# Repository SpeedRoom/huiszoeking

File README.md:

# huiszoeking
Meer info over het project is te vinden op https://speedroom.github.io/Huiszoeking.html

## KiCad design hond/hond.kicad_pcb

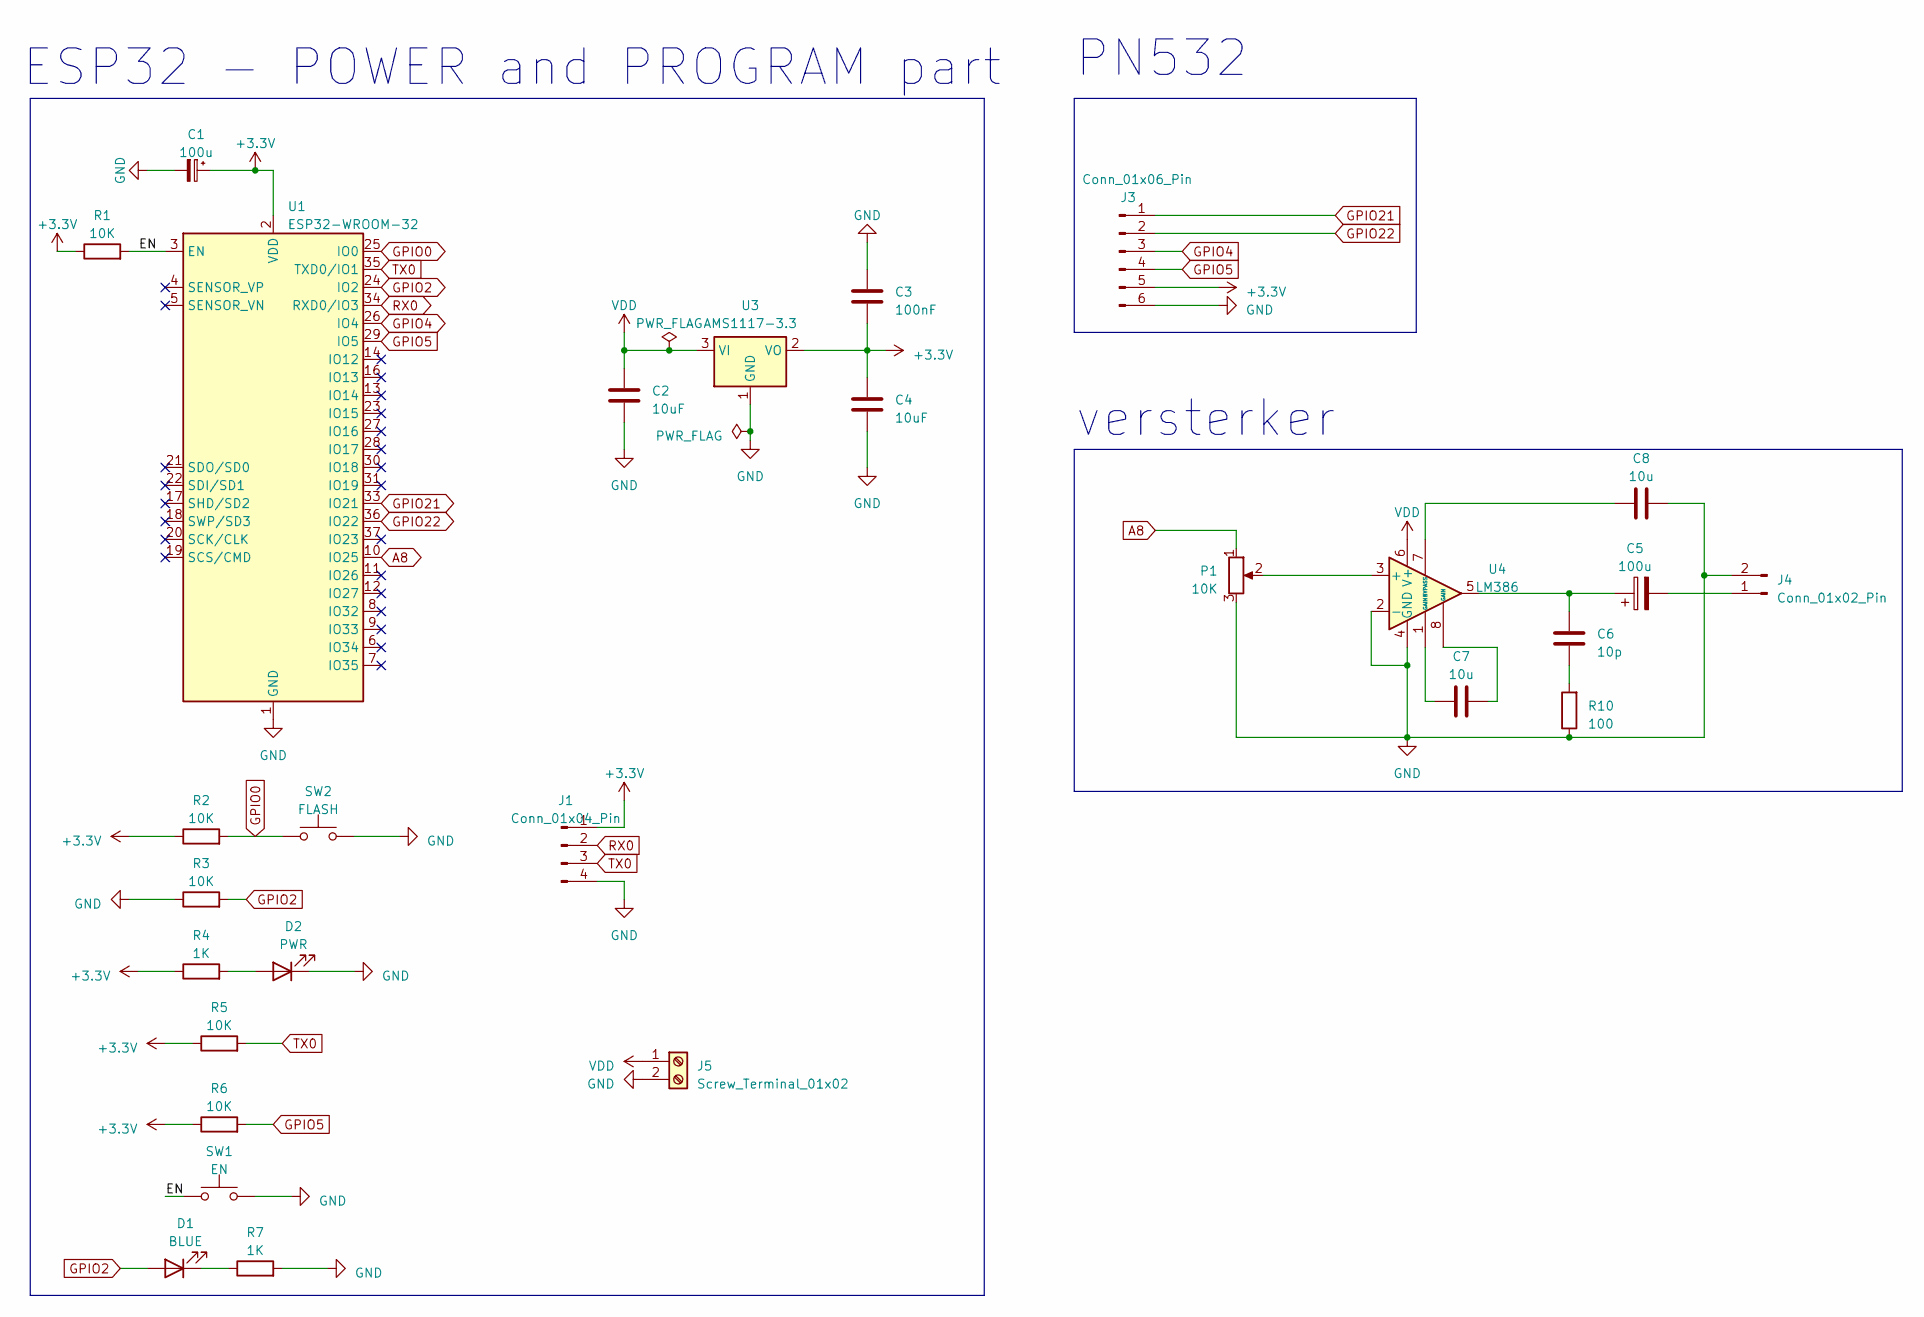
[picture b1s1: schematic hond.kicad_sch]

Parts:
C1, C5: 100u; C_0805_2012Metric_Pad1.18x1.45mm_HandSolder
C2, C4: 10uF; C_0805_2012Metric_Pad1.18x1.45mm_HandSolder
C3: 100nF; C_0805_2012Metric_Pad1.18x1.45mm_HandSolder
C6: 10p; C_0805_2012Metric_Pad1.18x1.45mm_HandSolder
C7, C8: 10u; C_0805_2012Metric_Pad1.18x1.45mm_HandSolder
D1: BLUE; LED_0805_2012Metric_Pad1.15x1.40mm_HandSolder
D2: PWR; LED_0805_2012Metric_Pad1.15x1.40mm_HandSolder
J1: Conn_01x04_Pin; PinHeader_1x04_P2.54mm_Vertical
J3: Conn_01x06_Pin; PinHeader_1x06_P2.54mm_Vertical
J4: Conn_01x02_Pin; PinHeader_1x02_P2.54mm_Vertical
J5: Screw_Terminal_01x02; TerminalBlock_bornier-2_P5.08mm
P1: 10K; Potentiometer_Bourns_3386P_Vertical
R1, R2, R3, R5, R6: 10K; R_0805_2012Metric_Pad1.20x1.40mm_HandSolder
R4, R7: 1K; R_0805_2012Metric_Pad1.20x1.40mm_HandSolder
R10: 100; R_0805_2012Metric_Pad1.20x1.40mm_HandSolder
SW1: EN; SW_DIP_SPSTx01_Slide_Copal_CHS-01B_W7.62mm_P1.27mm
SW2: FLASH; SW_DIP_SPSTx01_Slide_Copal_CHS-01B_W7.62mm_P1.27mm
U1: ESP32-WROOM-32
U3: AMS1117-3.3; SOT-223-3_TabPin2
U4: LM386; HVSSOP-8-1EP_3x3mm_P0.65mm_EP1.57x1.89mm

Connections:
+3.3V: C1.1, C3.2, C4.1, J1.1, J3.5, R1.1, R2.1, R4.1, R5.1, R6.1, U1.2 (VDD), U3.2 (VO)
/EN: R1.2, SW1.1, U1.3 (EN)
A8: P1.1, U1.10 (IO25)
GND: C1.2, C2.2, C3.1, C4.2, C8.2, D2.1 (K), J1.4, J3.6, J4.2, J5.2, P1.3, R3.1, R7.2, R10.1, SW1.2, SW2.2, U1.1 (GND), U1.15 (GND), U1.38 (GND), U1.39 (GND), U3.1 (GND), U4.2 (-), U4.4 (GND)
GPIO0: R2.2, SW2.1, U1.25 (IO0)
GPIO2: D1.2 (A), R3.2, U1.24 (IO2)
GPIO4: J3.3, U1.26 (IO4)
GPIO5: J3.4, R6.2, U1.29 (IO5)
GPIO21: J3.1, U1.33 (IO21)
GPIO22: J3.2, U1.36 (IO22)
unnamed: C5.1, C6.1, U4.5
unnamed: C6.2, R10.2
unnamed: C7.1, U4.1 (GAIN)
unnamed: C7.2, U4.8 (GAIN)
unnamed: D1.1 (K), R7.1
unnamed: D2.2 (A), R4.2
unnamed: C5.2, J4.1
unnamed: P1.2, U4.3 (+)
unnamed: C8.1, U4.7 (BYPASS)
RX0: J1.2, U1.34 (RXD0/IO3)
TX0: J1.3, R5.2, U1.35 (TXD0/IO1)
VDD: C2.1, J5.1, U3.3 (VI), U4.6 (V+)

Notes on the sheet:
PN532
ESP32 - POWER and PROGRAM part
versterker

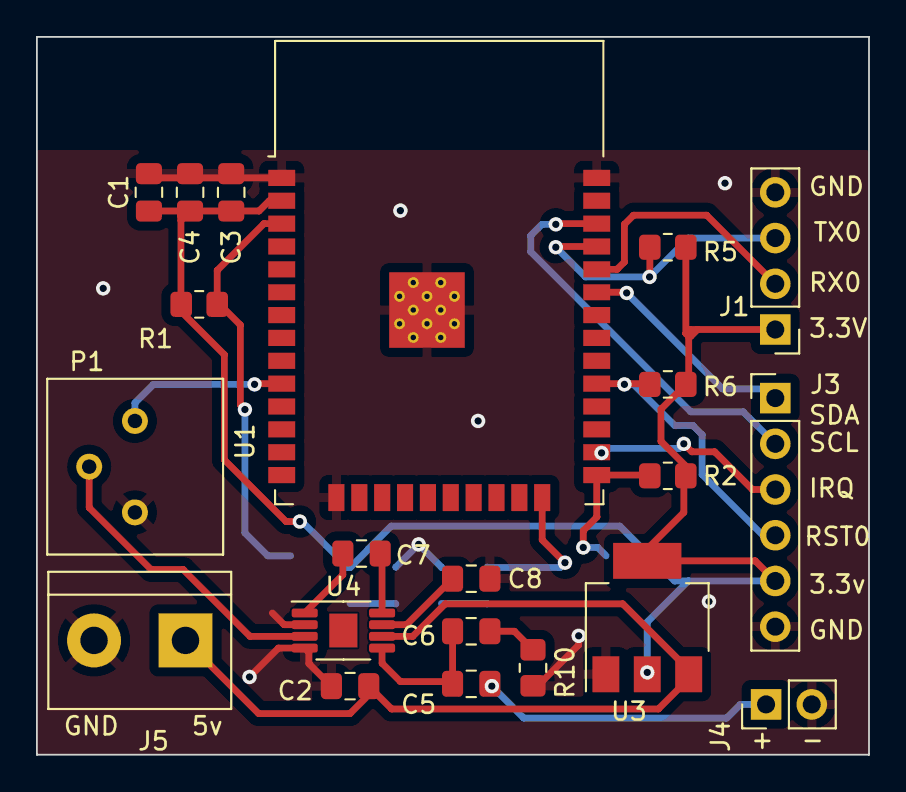
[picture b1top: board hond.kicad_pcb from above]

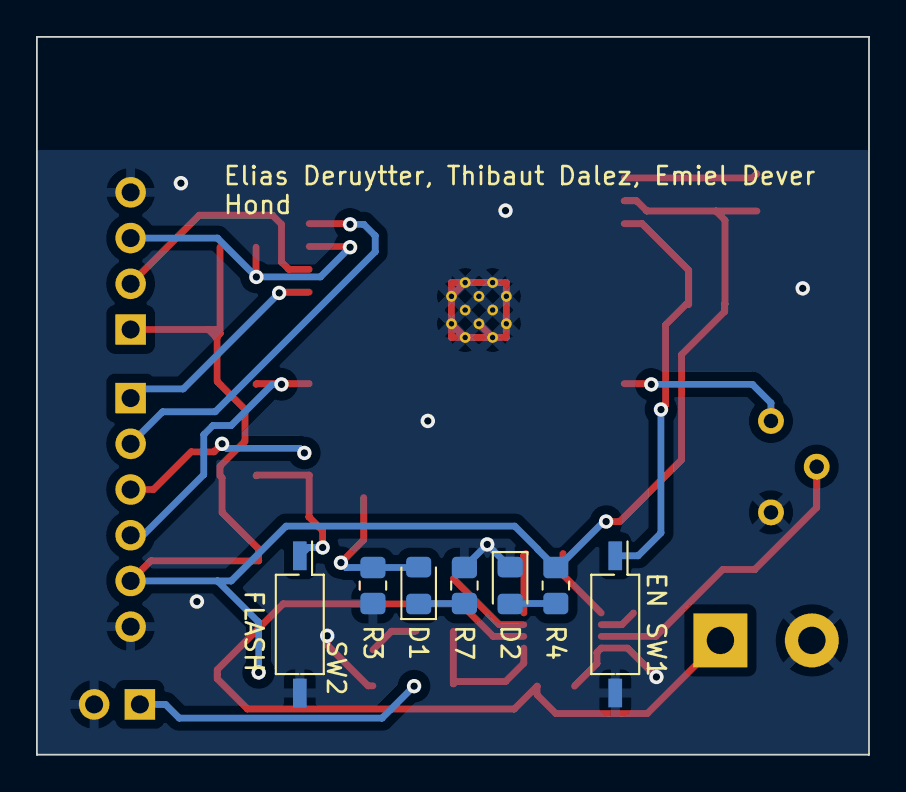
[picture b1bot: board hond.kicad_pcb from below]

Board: 2 copper layers, 46.2 x 39.9 mm, 28 parts (7 on the bottom side), 22 nets.

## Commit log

2023-02-25 RFID
    werkende code voor de pn532 RFID module (de roden) met aangepaste connecties
2023-02-27 gwn mappen anders benoemd
2023-02-27 nog eens mappen veranderd
2023-02-27 drugszakjes
2023-02-28 ledjes
    de led van de weegschaal begint te branden wanneer er 3 specifiteke nfc tags gepresenteerd worden
2023-02-28 ledje
    ledje gaat branden door de stickers nu ipv de badge
2023-02-28 hond met fouten in de seriele monitor
2023-03-04 uitlezen van het adres zender beacon lukt
2023-03-07 weegschaal update
    De weegschaal kan nu scannen en het gewicht uitlezen en doorgeven van wanneer er een zakje aanwezig is in de bak
2023-03-07 speaker
    de speaker maakt geluid voor luid en stil blaffen
2023-03-07 hond blaf maar bij bepaalde afstand
2023-03-11 update proberen accurater te maken
    -gemiddelde over 5 ontvangen signalen nemen
    -problemen stack zijn ook weg denk ik
    -rssi /10 om intensiteit signaal te verdelen in waardes zoals 2 3 4 5 6 7 8. voor sterkte geluid.
    nog altijd niet super accuraat. rssi schommelt willekeurig ookal laat je ze alle twee liggen.
2023-03-12 Geluid
    muziek gefixt met hex code
    te stil wel!
    kdenk da mp 3 kan omgezet worden naar . h file en dan moet je const en PROGMEM toevoegen eraan. zie github pagina van library:
    https://github.com/earlephilhower/ESP8266Audio
2023-03-28 OTA added
2023-03-28 OTA updated
2023-04-17 geluid update
    hond blaft, maar telkens inladen duurt lang, geluik ook wa zwak, maar is nie zoveel aan te doen denk ik
2023-04-19 met da werket om het met da usb ding up te loaden, ota niet!
2023-04-20 pcb design weegschaal
2023-04-20 verkeerde files
2023-04-25 gsjfmlk
2023-05-02 pcb weegschaal
2023-05-02 raar
2023-05-02 verdwenen bestanden terug
2023-05-02 2e geluid opgezet
2023-05-08 voorlopig geluid in groot programma, werkt nog niet
2023-05-08 testen
2023-05-10 code update hond
2023-05-10 testen hond
2023-05-11 Update main.cpp
    Added some visual feedback to the code
2023-05-11 Code cleanup
    adding aditional functions to reduce unneeded code
2023-05-12 hond main update
2023-05-12 reverse hond pcb
2023-05-12 pcb_hond
2023-05-13 werkend + opgeschoond
    programma werkte plots niet meer door rfid, irq was het probleem, gwn irq niet gebruiken lost het probleem op.
2023-05-14 pcb update
2023-05-15 updat
2023-05-15 3d weegschaal
2023-05-15 Revert "csv"
    This reverts commit dff9284bcc8244e921bcfb7733e73e2f2b8e4a2d.
